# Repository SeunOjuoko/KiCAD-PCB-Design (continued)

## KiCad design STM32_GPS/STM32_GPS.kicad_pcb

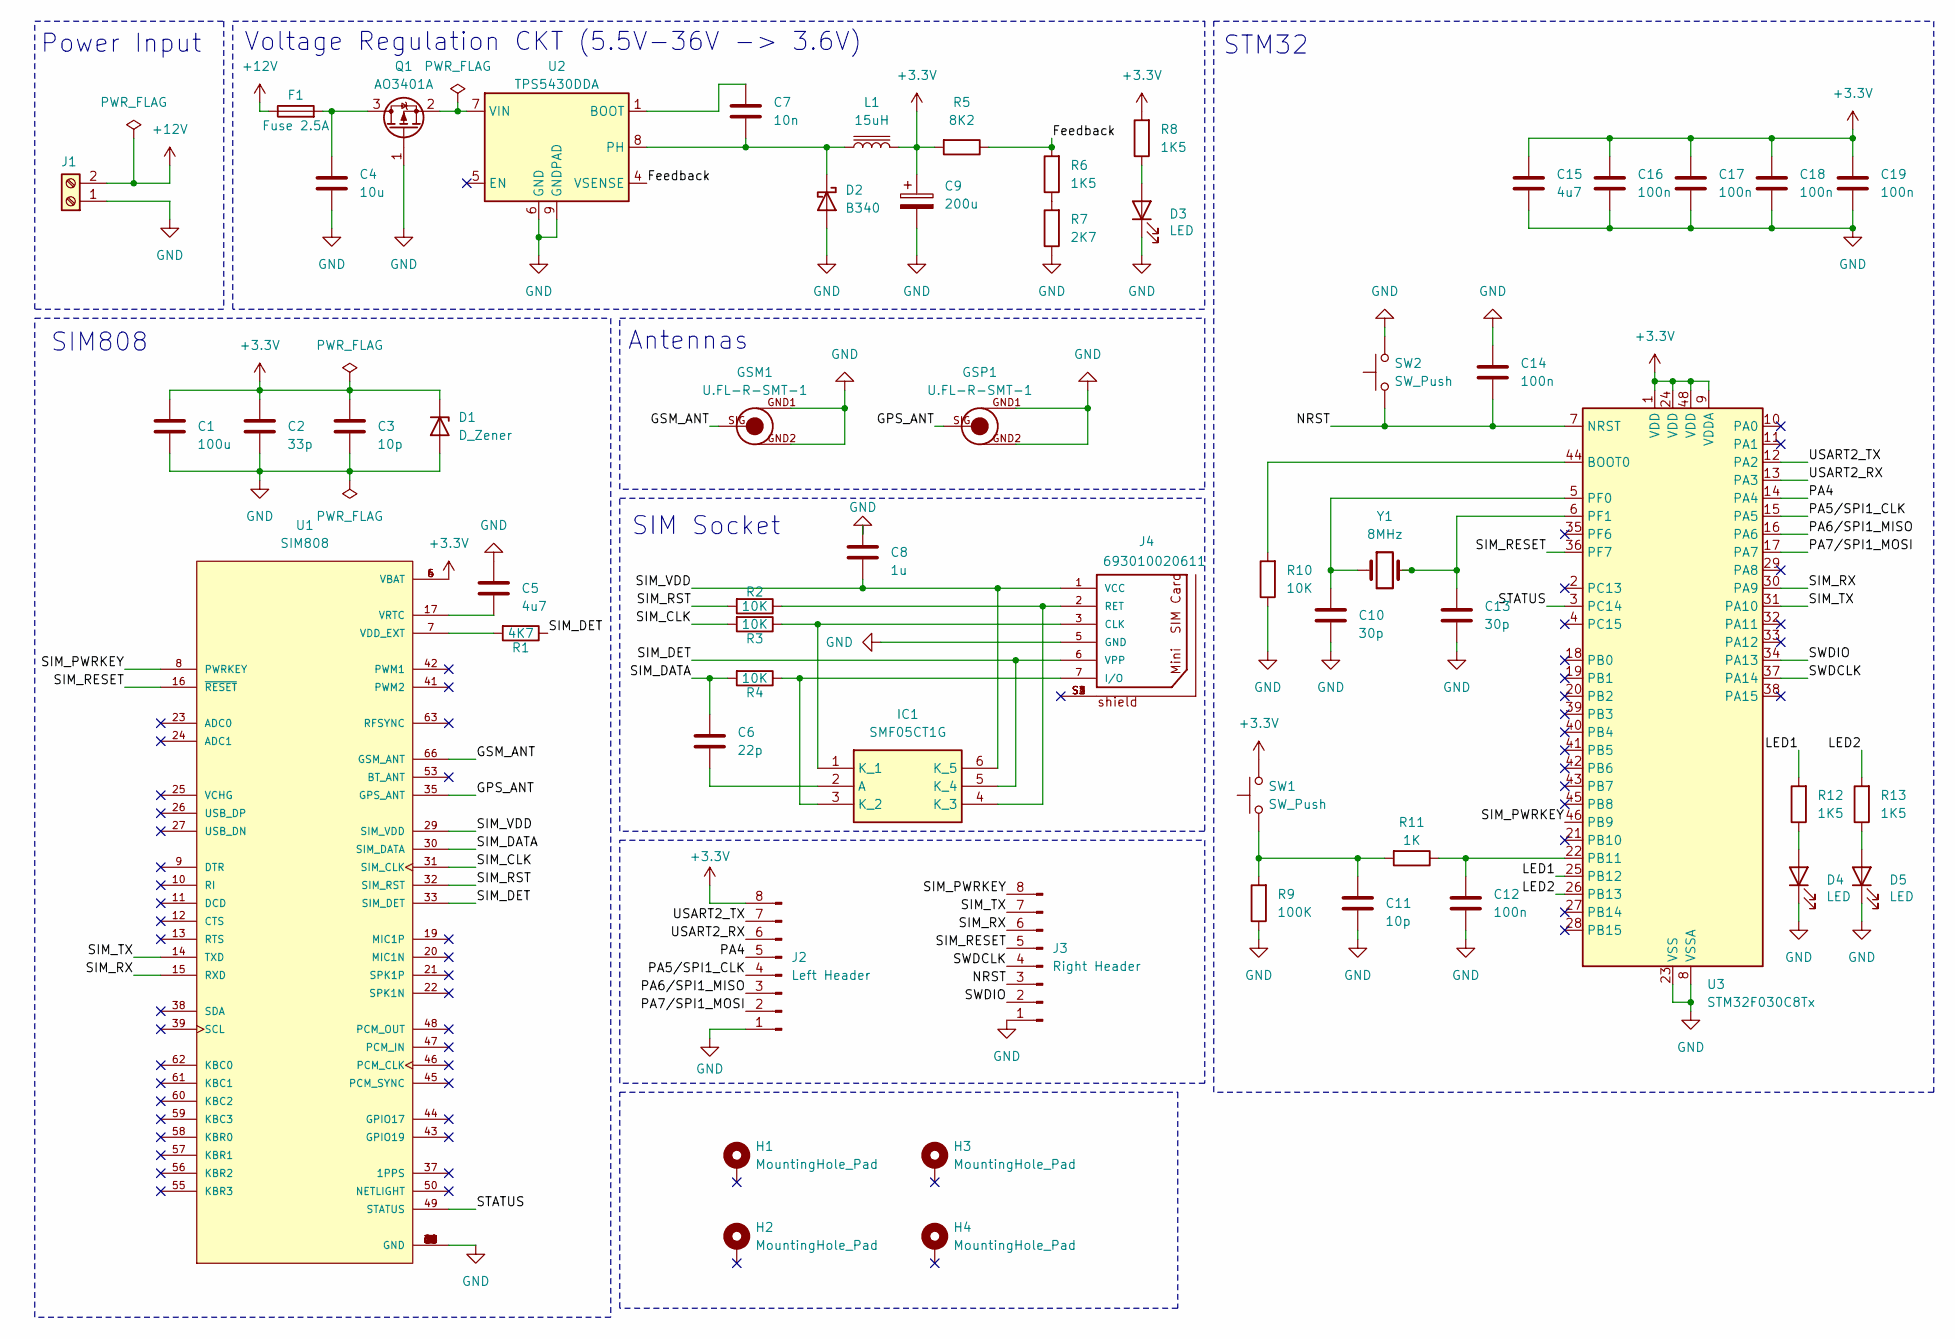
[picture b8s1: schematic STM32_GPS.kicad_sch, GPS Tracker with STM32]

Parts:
C1: 100u; C_1206_3216Metric
C2: 33p; C_0402_1005Metric
C3: 10p; C_0805_2012Metric
C4: 10u; C_0402_1005Metric
C5, C15: 4u7; C_0201_0603Metric
C6: 22p; C_0402_1005Metric
C7: 10n; C_0201_0603Metric
C8: 1u; C_0402_1005Metric
C9: 200u; CP_EIA-7343-15_Kemet-W
C10, C13: 30p; C_0402_1005Metric
C11: 10p; C_0402_1005Metric
C12, C14, C16, C17, C18, C19: 100n; C_0402_1005Metric
D1: D_Zener; D_0805_2012Metric
D2: B340; D_SMC
D3, D4, D5: LED; LED_0603_1608Metric
F1: Fuse 2.5A; Fuse_0402_1005Metric
GSM1: U.FL-R-SMT-1
GSP1: U.FL-R-SMT-1
H1, H2, H3, H4: MountingHole_Pad; MountingHole_2.2mm_M2_Pad_Via
IC1: SMF05CT1G; SOT65P210X110-6N; Mouser Part Number 863-SMF05CT1G
J1: Screw_Terminal_01x02; TerminalBlock_bornier-2_P5.08mm
J2: Left Header; PinHeader_1x08_P2.54mm_Vertical
J3: Right Header; PinHeader_1x08_P2.54mm_Vertical
J4: 693010020611
L1: 15uH; L_10.4x10.4_H4.8
Q1: AO3401A; SOT-23
R1: 4K7; R_0402_1005Metric
R2, R3, R4, R10: 10K; R_0402_1005Metric
R5: 8K2; R_0805_2012Metric
R6, R8, R12, R13: 1K5; R_0805_2012Metric
R7: 2K7; R_0805_2012Metric
R9: 100K; R_0201_0603Metric
R11: 1K; R_0603_1608Metric
SW1, SW2: SW_Push; SW_Push_1P1T_NO_CK_KSC6xxJ
U1: SIM808; XCVR_SIM808; PARTREV 1.03
U2: TPS5430DDA; TI_SO-PowerPAD-8_ThermalVias
U3: STM32F030C8Tx; LQFP-48_7x7mm_P0.5mm
Y1: 8MHz; Crystal_SMD_5032-2Pin_5.0x3.2mm

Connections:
+3.3V: C1.1, C2.1, C3.1, C9.1, C15.1, C16.1, C17.1, C18.1, C19.1, D1.1 (K), J2.8, L1.2, R5.2, R8.2, SW1.2, U1.4 (VBAT), U1.5 (VBAT), U1.6 (VBAT), U3.1 (VDD), U3.9 (VDDA), U3.24 (VDD), U3.48 (VDD)
+12V: F1.1, J1.2
/Feedback: R5.1, R6.2, U2.4 (VSENSE)
/GPS_ANT: GSP1.SIG, U1.35 (GPS_ANT)
/GSM_ANT: GSM1.SIG, U1.66 (GSM_ANT)
/LED1: R12.2, U3.25 (PB12)
/LED2: R13.2, U3.26 (PB13)
/NRST: C14.2, J3.3, SW2.1, U3.7 (NRST)
/PA4: J2.5, U3.14 (PA4)
/PA5/SPI1_CLK: J2.4, U3.15 (PA5)
/PA6/SPI1_MISO: J2.3, U3.16 (PA6)
/PA7/SPI1_MOSI: J2.2, U3.17 (PA7)
/SIM_CLK: R3.2, U1.31 (SIM_CLK)
/SIM_DATA: C6.1, R4.2, U1.30 (SIM_DATA)
/SIM_DET: IC1.5 (K_4), J4.6 (VPP), R1.1, U1.33 (SIM_DET)
/SIM_PWRKEY: J3.8, U1.8 (PWRKEY), U3.46 (PB9)
/SIM_RESET: J3.5, U1.16 (~RESET), U3.36 (PF7)
/SIM_RST: R2.2, U1.32 (SIM_RST)
/SIM_RX: J3.6, U1.15 (RXD), U3.30 (PA9)
/SIM_TX: J3.7, U1.14 (TXD), U3.31 (PA10)
/SIM_VDD: C8.2, IC1.6 (K_5), J4.1 (VCC), U1.29 (SIM_VDD)
/STATUS: U1.49 (STATUS), U3.3 (PC14)
/SWDCLK: J3.4, U3.37 (PA14)
/SWDIO: J3.2, U3.34 (PA13)
/USART2_RX: J2.6, U3.13 (PA3)
/USART2_TX: J2.7, U3.12 (PA2)
GND: C1.2, C2.2, C3.2, C4.2, C5.1, C8.1, C9.2, C10.2, C11.2, C12.2, C13.2, C14.1, C15.2, C16.2, C17.2, C18.2, C19.2, D1.2 (A), D2.2 (A), D3.1 (K), D4.1 (K), D5.1 (K), GSM1.GND1, GSM1.GND2, GSP1.GND1, GSP1.GND2, J1.1, J2.1, J3.1, J4.5 (GND), Q1.1 (G), R7.1, R9.1, R10.1, SW2.2, U1.1 (GND), U1.2 (GND), U1.3 (GND), U1.18 (GND), U1.28 (GND), U1.34 (GND), U1.36 (GND), U1.40 (GND), U1.51 (GND), U1.52 (GND), U1.54 (GND), U1.64 (GND), U1.65 (GND), U1.67 (GND), U1.68 (GND), U2.6 (GND), U2.9 (GNDPAD), U3.8 (VSSA), U3.23 (VSS), U3.47 (VSS)
unnamed: C11.1, R9.2, R11.2, SW1.1
unnamed: C7.2, D2.1 (K), L1.1, U2.8 (PH)
unnamed: D3.2 (A), R8.1
unnamed: D4.2 (A), R12.1
unnamed: D5.2 (A), R13.1
unnamed: C6.2, IC1.2 (A)
unnamed: IC1.1 (K_1), J4.3 (CLK), R3.1
unnamed: IC1.3 (K_2), J4.7 (I/O), R4.1
unnamed: IC1.4 (K_3), J4.2 (RET), R2.1
unnamed: C4.1, F1.2, Q1.3 (D)
unnamed: Q1.2 (S), U2.7 (VIN)
unnamed: R6.1, R7.2
unnamed: R1.2, U1.7 (VDD_EXT)
unnamed: C5.2, U1.17 (VRTC)
unnamed: C7.1, U2.1 (BOOT)
unnamed: R10.2, U3.44 (BOOT0)
unnamed: C12.1, R11.1, U3.22 (PB11)
unnamed: C10.1, U3.5 (PF0), Y1.1
unnamed: C13.1, U3.6 (PF1), Y1.2

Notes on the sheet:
SIM808
Voltage Regulation CKT (5.5V-36V -> 3.6V)
Power Input
SIM Socket
Antennas
STM32

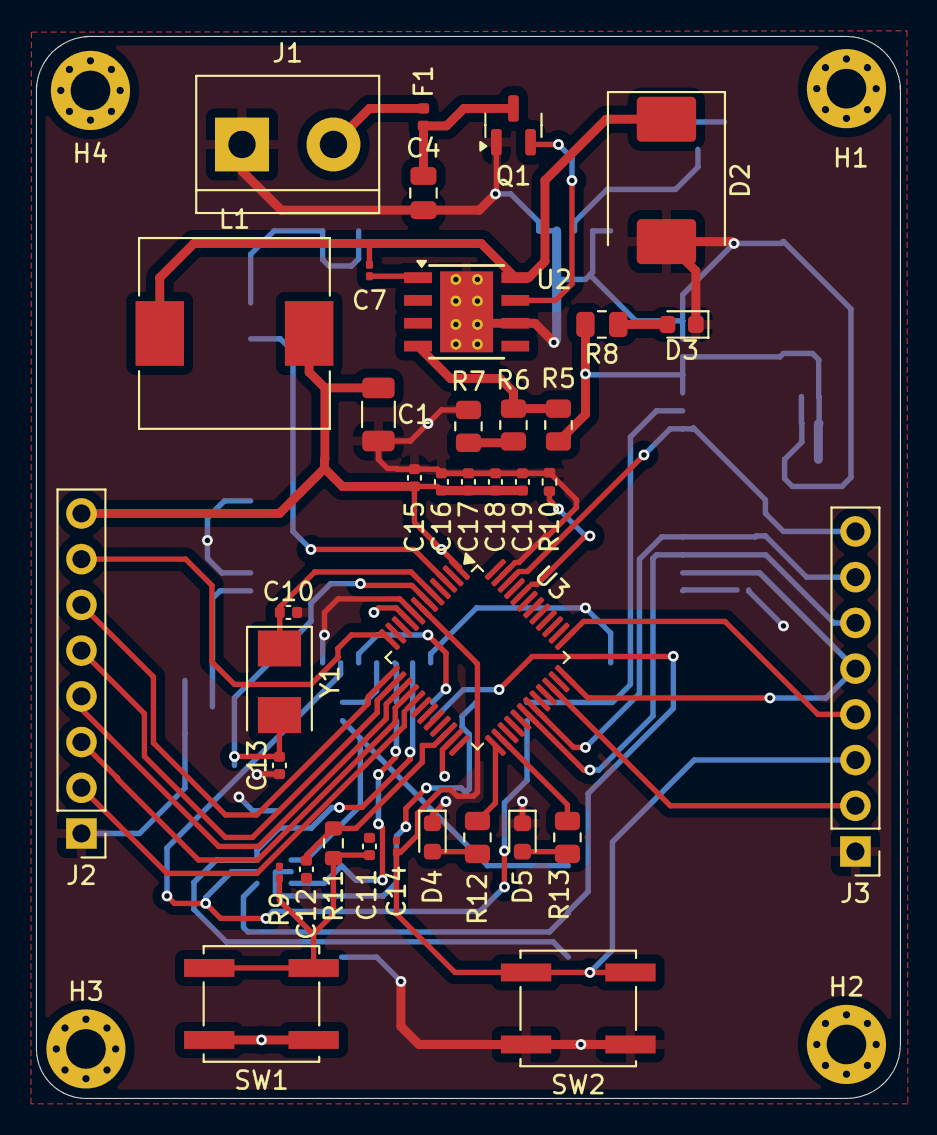
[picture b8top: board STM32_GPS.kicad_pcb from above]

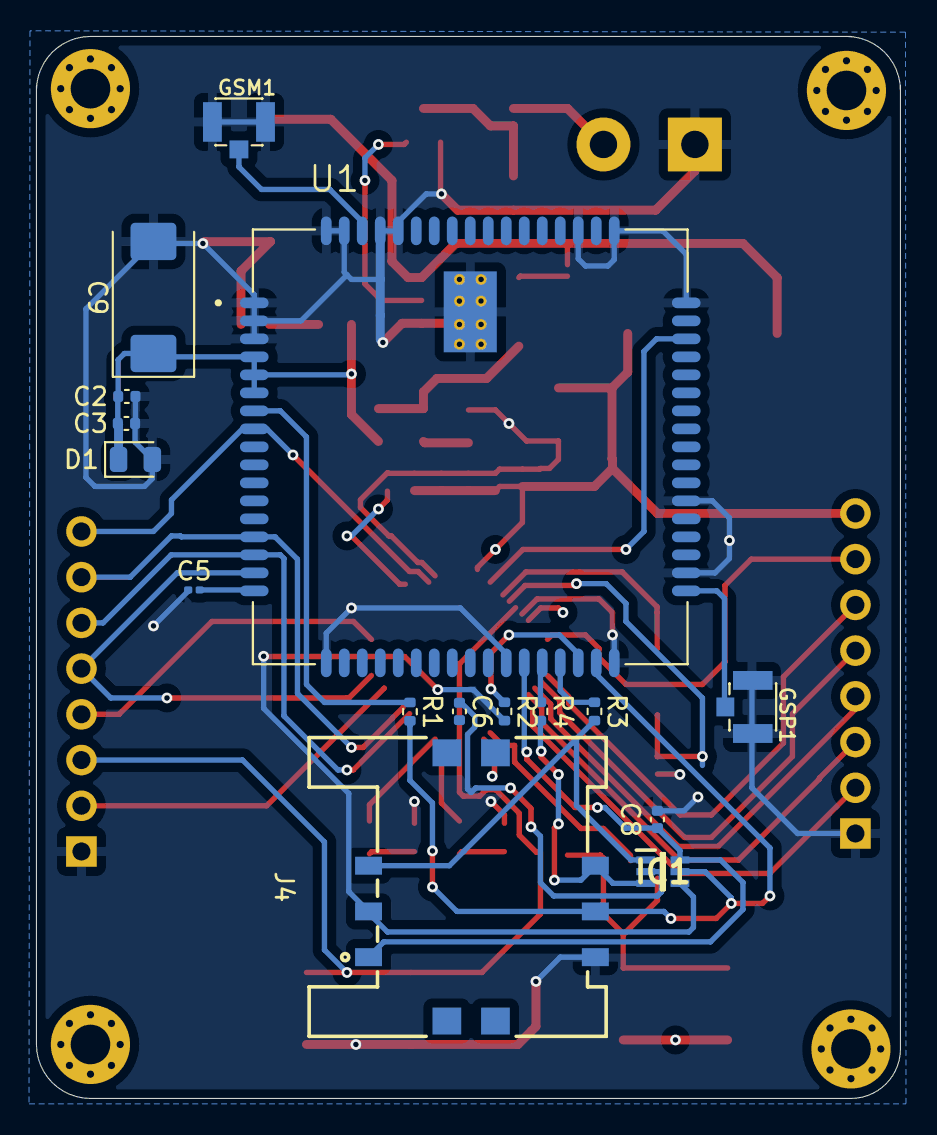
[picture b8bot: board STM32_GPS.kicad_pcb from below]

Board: 4 copper layers, 48.0 x 59.0 mm, 57 parts (16 on the bottom side), 46 nets.

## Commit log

2026-06-07 Create Optobot PCB
